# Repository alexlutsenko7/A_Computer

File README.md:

# L

Retro computers in an FPGA: an Intel/Altera Cyclone IV E (EP4CE15F23C8) on a QMTECH core board, with the RAM and
ROMs in the board's SDRAM, VGA output, a USB keyboard and an ESP32 system controller (SD card loader, on-screen
menus, Bluetooth audio). A machine menu at power-up chooses the machine:

- **LSpectrum**, a ZX Spectrum 128K with a built-in SD card tape loader that plays unmodified `.tap` / `.tzx` files,
  saves programs back to the card, and saves / loads `.z80` snapshots;
- **L64**, a Commodore 64 (PAL) with a 1541 disk drive that reads and writes `.d64` images, `.prg` / `.t64`
  loading, C64 `.tap` tapes, turbo loading and `.a64` snapshots;
- **LTari**, an Atari 800XL (**LTari 800**, 64 KB) or 130XE (**LTari 130**, 128 KB) with its own ANTIC, GTIA, POKEY
  and PIA, an SD card disk drive (`.atr`), `.xex` / `.com` programs, cartridges (`.car`) and `.a8s` snapshots.

Status (October 2026): the menu, LSpectrum, L64 and LTari work on hardware.

**Licences, what is our own work, and the complete build guide (including the C64 ROM files you have to get
yourself): [BUILDING_AND_LICENSES.md](BUILDING_AND_LICENSES.md).**

## Features

- **ZX Spectrum 128K**: T80 Z80 core at the exact 3.5469 MHz, or 28 MHz turbo; 128 KB RAM with 7FFD paging; 128K
  ROM set and DiagROM; AY-3-8912 (JT49); beeper; Kempston joystick; 50 Hz interrupt; memory contention (128K
  timing, memory and I/O cycles; not cycle-exact) and the floating bus, so most timing-critical games and border
  effects run as on the real machine.
- **Memory in SDRAM**: own 112 MHz controller for the W9825G6KH (open-row, CAS latency 2); the CPU is stepped by a
  clock enable and simply waits when the SDRAM is busy. The screen is mirrored in block RAM for the video.
- **Video**: VGA 720x576@50 (576p) or 640x480@60, 2 bits per colour, switchable at run time.
- **USB keyboard** through a CH9350-style UART module, with machine keys: DiagROM, 50/60 Hz, reset.
- **SD card tape loader** on an ESP32 system controller (firmware in C, SPI link to the FPGA):
  - on-screen browser (folders, long names, up to 320 entries), FAT16 / FAT32;
  - plays TAP and TZX (incl. turbo blocks, pure tones, pulse sequences, direct recordings, loops, jumps, calls,
    stop blocks) T-state exact, in turbo (8x) or at normal speed;
  - saves: everything the Spectrum `SAVE`s goes into a `.tap` file on the card;
  - pause, back one block, stop;
  - **snapshots**: F2 saves the whole machine as a `.z80` (version 3, 128K) at any moment; the browser loads
    `.z80` files (versions 1-3, 48K and 128K).
- **Bluetooth audio**: the same ESP32-WROOM-32 (`ESP32/v2/`, Arduino) takes the sound as I2S and sends it to Bluetooth
  speakers / headphones (A2DP), including old PIN-only devices; F3 opens the on-screen Bluetooth menu.
- **L64** (`L64/ep4_ce15/README.md`): VIC-II Kawari, T65 as 6510, the MiSTer SID 6581/8580 and CIAs, our bus, PLA
  and 1541 drive (T65, two VIAs, GCR on the fly from a track buffer the ESP32 fills from the `.d64`). The
  picture goes through a frame buffer in SDRAM: 800x600 at 60 Hz, or the C64's own 50 Hz (F8). Turbo loading (F6):
  CPU, CIAs and 1541 up to 4x while a motor runs. F2 snapshots (`.a64`). The C64 ROMs are not part of the project:
  the ESP32 installs your own ROM files from the SD card into the flash.
- **Machine menu** (`AMenu/ep4_ce15/`): the factory image at flash 0 starts a machine through the Cyclone IV remote update
  block; KEY1 in a machine returns to it.
- **Fully constrained timing**: every clock and I/O constrained, timing met at all corners.

## Hardware

| Part | Notes |
|---|---|
| QMTECH Cyclone IV core board | EP4CE15F23C8N, 50 MHz oscillator, W9825G6KH-6 SDRAM (32 MB), W25Q64 configuration flash |
| I/O board (own design, `Extra_PCB_CycloneIV/`) | 4-bit-per-colour VGA DAC, two Kempston DB9, 3.5 mm audio jack (AY + beeper, line level), USB keyboard module (UART, 3.3 V), microSD socket, sockets for the ESP32; wired to the core board's U8 |
| I/O board revision 2 (own design, `Extra_PCB_CycloneIV_R2/`, ordered 2026-11-03) | as revision 1, with everything on the board: ESP32-WROVER-E module, CP2102N USB-C console / 5 V input, CH9350L with a USB-A keyboard socket, a second USB-A (5 V for a VGA2HDMI dongle); 4 layers; same J1 to the core board's U8 |
| ESP32-WROOM-32 dev board | system controller on the I/O board: SD card, tape loader, Bluetooth audio (`ESP32/v2/README.md`) |

Pin assignments: `docs/BOARD_PINOUT.md`.

## Repository layout

AMenu, LSpectrum, L64, LTari and DDR_TEST each hold one subfolder per core board: `ep4_ce15/` (QMTECH Cyclone IV EP4CE15: all sources, simulations and tools) and `10cl025/` (QMTECH Cyclone 10 LP 10CL025YU256: the Quartus project only, generated by `tools/mk_10cl025_qsf.py`; it uses the sources of `ep4_ce15/`). The 10CL025 builds meet timing but have **not been tried on hardware** yet. An `L.jic` or `LUPDATE.BIN` is for one board only: `AMenu/<board>/output_files/`.

| Folder | Contents |
|---|---|
| `AMenu/ep4_ce15/` | machine menu shown at power-up (factory image); `L.cof` -> `output_files/L.jic`, the ready-to-program image with all machines |
| `LSpectrum/ep4_ce15/` | **The Spectrum**: Quartus project, `rtl/` (Verilog), `sim/` (Questa testbenches) |
| `ESP32/` | **the ESP32 firmware**, the same for all machines and both FPGA boards (loader + Bluetooth): `v1/` for I/O board revision 1 (in use), `v2/` for revision 2; each an Arduino sketch (`v1.ino` / `v2.ino`) with its sources in `src/` |
| `ESP32_test/` | tests of the firmware: `v1/`, `v2/` with the PC tests (`test/`) and their tools (`tools/`); `v1/` also holds the hardware test sketches `ESPLinkTest/` (SPI link) and `Test_wires/` (ESP32 <-> FPGA wiring) |
| `L64/ep4_ce15/` | **The Commodore 64**: Quartus project, `rtl/` (our bus, 1541, video; Kawari VIC-II, SID, CIA, VIA), `sim/`, `tools/` (ROM image, test disk) |
| `T65/` | 6502 core (VHDL), from the MiSTer C64 core, unchanged (`T65/SOURCE.md`) |
| `tests/` | FPGA test projects: `Test_wires/fpga/` (ESP32 <-> FPGA wiring, FPGA side; the sketch is `ESP32_test/v1/Test_wires/`), `t80_fmax/`, `jtag_rig/` (testing a core board without its I/O board: keys, status and the video picture over JTAG) |
| `T80/` | Z80 core (VHDL), from the MiSTer ZX Spectrum core, unchanged (`T80/SOURCE.md`) |
| `DDR_TEST/` | stand-alone SDRAM controller + memory test (the controller used by LSpectrum): `ep4_ce15/` for the Cyclone IV EP4CE15 core board, `10cl025/` the same test for the QMTECH Cyclone 10 LP 10CL025 core board |
| `VGA_TEST/` | stand-alone VGA test (colour bars, both video modes) |
| `Extra_PCB_CycloneIV/` | **the I/O board, revision 1**: KiCad 10 project (schematic + PDF, routed 2-layer layout, project symbols / footprints), JLCPCB order files (`jlcpcb/`: Gerbers, drill, BOM, CPL), wiring to the core board (`README.md`) |
| `Extra_PCB_CycloneIV_R2/` | **the I/O board, revision 2**: KiCad 10 project (schematic + PDF, routed 4-layer layout with GND / +3V3 planes, project footprints incl. the ESP32-WROVER-E), JLCPCB order files (`jlcpcb/`), generator / routing scripts (`tools/`), `README.md` |
| `docs/` | design notes, user documents, data sheets (see below) |

## Building

Step by step, from the tools to the SD card: [BUILDING_AND_LICENSES.md](BUILDING_AND_LICENSES.md), section 4.
Tools: Quartus Prime 25.1std Lite (Windows) for the FPGA; Arduino (core esp32 3.3.2, `arduino-cli`) for the ESP32
(libraries: `ESP32/v2/README.md`). The scripts are written for WSL on Windows and call the Windows tools;
paths are at the top of each script.

```
cd LSpectrum/ep4_ce15
quartus_sh --flow compile LSpectrum              # -> output_files/LSpectrum.sof
cd ../L64
quartus_sh --flow compile L64                # -> output_files/L64.sof
cd ../AMenu
quartus_sh --flow compile AMenu                  # machine menu
quartus_cpf -c L.cof                      # -> output_files/L.jic (menu + machines + ROMs)
cd ../..
arduino-cli compile -b esp32:esp32:esp32 -u -p COM10 ESP32/v1    # ESP32 firmware (loader + Bluetooth), I/O board revision 1
```

Flash layout (1 MB per image): menu at 0, LSpectrum at 0x100000, L64 at 0x200000, LTari 800 at 0x300000, LTari 130 at
0x400000, the Spectrum ROMs (`roms48k.hex`) at 0x500000, the Atari ROMs at 0x540000, the C64 ROMs (installed by the
ESP32) at 0x580000; ROMs are copied into SDRAM at every reset.
A change in `ESP32/v2/` needs only the ESP32 flashed again; a change in `LSpectrum/ep4_ce15/rtl/` a new compile.

## Programming

Quartus Programmer, JTAG, add `AMenu/ep4_ce15/output_files/L.jic`, tick Program/Configure, program, then
power-cycle the board. After that, `.sof` loads over JTAG are enough during development (the ROMs stay in the flash).

## Using it

The keys below are LSpectrum's; L64's (mostly the same F keys) are in `docs/L64_Keys.docx` and `L64/ep4_ce15/README.md`.

| Key | Function |
|---|---|
| F12 | tape browser (Enter plays a tape / loads a `.z80` snapshot; first line *[Save to this folder]* starts saving) |
| F2 | save a snapshot: type a name, Enter (`NAME.Z80` in the browser's current folder) |
| F12 while saving | stop saving and close the file |
| Keypad 5 / F11 | pause / continue the tape |
| Keypad - | back one block |
| F7 | stop the tape |
| F5 | memory contention and floating bus on (default) / off |
| F6 | tape speed: turbo (default) / normal |
| F8 | 60 / 50 Hz video (starts at 640x480@60; border effects line up only at 50 Hz) |
| Page Up / Page Down | browser open: page through the list; closed: move the 50 Hz frame interrupt 1/8 line to line up border effects (default 24.1, set for Aquaplane) |
| F1 held at start | the diagnostics ROM slot instead of the 128K ROM (the public image has 48K BASIC there; add DiagROM yourself with `LSpectrum/ep4_ce15/tools/mk_roms48k.py`) |
| KEY0 (board) | reset everything |
| Ctrl+Alt+Del, KEY1 (board) | back to the machine menu (Ctrl+Alt+Del when released) |

Loading: `LOAD ""` (or *Tape Loader* in the 128K menu), F12, choose the file, Enter.
Saving: F12, *[Save to this folder]*, type a name, Enter, then `SAVE` on the Spectrum as often as you like; F12 ends.
Snapshot: F2 at any moment, type a name, Enter; load it later from the F12 browser.
SD card: FAT32 or FAT16 (not exFAT).

At power-up the machine menu (`AMenu/ep4_ce15/`) appears: Up/Down + Enter, the digit, or a joystick starts a machine.

The complete key list with step-by-step usage is in `docs/LSpectrum_Keys.docx`.

## Testing

```
bash ESP32_test/v2/test/run_host_test.sh       # PC: FAT reading/writing, every TAP/TZX signal vs a Python reference, saving, .z80
bash LSpectrum/ep4_ce15/sim/run_esp_link_sim.sh           # RTL: loader hardware driven over the SPI link by an ESP32 model
bash LSpectrum/ep4_ce15/sim/run_sim.sh                    # RTL: whole machine boots the 128K ROM
bash LSpectrum/ep4_ce15/sim/run_snap_sim.sh               # RTL: snapshot freeze / restore with the real T80
bash LSpectrum/ep4_ce15/sim/run_cont_sim.sh               # RTL: memory contention (NOPs per line in contended RAM: 57 / 41)
bash LSpectrum/ep4_ce15/sim/run_float_sim.sh              # RTL: floating bus (IN A,(FF) against Fuse's 128K rule)
bash LSpectrum/ep4_ce15/sim/run_floatgame_sim.sh          # RTL: a .z80 game's floating-bus sync vs Fuse (default Sidewize)
bash AMenu/ep4_ce15/sim/run_sim.sh                        # RTL: machine menu with a model of the remote update block
bash L64/ep4_ce15/sim/run_sim.sh ROMIMAGE.mem         # RTL: whole C64 boots to READY (your own ROM image); +define+DISK: 1541 directory
bash L64/ep4_ce15/sim/run_gcr_sim.sh                  # RTL: 1541 GCR encoder / decoder
```

The PC tests need a Windows gcc (w64devkit); the simulations need Questa (Intel FPGA Starter Edition).

## Documentation

| Document | Contents |
|---|---|
| `docs/LSpectrum_Architecture.docx` | architecture of the whole machine: block diagram, clocks, memory, video, tape loader, pins, timing |
| `docs/LSpectrum_Keys.docx` | all keys and usage cases |
| `docs/LSpectrum_FKeys.docx` | short sheet of the F keys |
| `docs/L_Build_and_Install.docx` | step by step: building the three FPGA images, the one .jic, programming, the ESP32, the SD card and its ROM files, how the ROMs are used |
| `docs/L64_Keys.docx` | the machine menu and L64: all keys, the C64 keyboard layout, usage cases (ROMs, disk, tape, snapshots, 60 / 50 Hz) |
| `docs/SD_TAPE_LOADER.md` | SD tape loader: design, registers, firmware, saving, snapshots |
| `docs/SDRAM_CONTROLLER.md`, `docs/SDRAM_TUTORIAL.md` | the SDRAM controller in detail, and an SDRAM tutorial |
| `docs/T80_CEN_ANALYSIS.md` | running the T80 from a clock enable at 112 MHz |
| `docs/BOARD_PINOUT.md` | core board headers and the I/O board wiring |
| `docs/KNOWN_ISSUES.md` | open issues and limitations |
| `docs/L_Third_Party.docx` | every external core and library: origin, licence, how much of it is used |
| `docs/PLAN.md` | design decisions and development log |

## Licences

The project's own files are under the MIT licence (`LICENSE`). Third-party parts keep their own licences:

| Part | Licence |
|---|---|
| `T80/` (Z80 core, Daniel Wallner; Sorgelig) | BSD-style, see the file headers |
| `T65/` (6502 core, Daniel Wallner et al.) | BSD-style, see the file headers |
| `LSpectrum/ep4_ce15/rtl/jt49/` (AY-3-8910 core, Jose Tejada) | **GPL-3**: a bitstream that includes it is a GPL-3 work |
| `L64/ep4_ce15/rtl/vicii/` (VIC-II Kawari, Randy Rossi) | **GPL-3** |
| `L64/ep4_ce15/rtl/via/` (VIA 6522, Gideon Zweijtzer) | **GPL-3** |
| `L64/ep4_ce15/rtl/sid/`, `L64/ep4_ce15/rtl/cia/` (MiSTer C64 core) | CERN-OHL-S v2 (`sid_dac.sv`, `sid_filter.sv`) and GPL (the MiSTer C64 core) |
| `ESP32/v2/` uses ESP32-A2DP (Phil Schatzmann) | Apache-2.0 (library, not included) |
| ROM images in `LSpectrum/ep4_ce15/roms48k.hex` and `LSpectrum/ep4_ce15/sim/roms.mem` | ZX Spectrum 128 ROMs (c) Amstrad, distributed for emulator use with permission, copyright messages unchanged. Retroleum's DiagROM is not included (its licence is not known): the published image has a copy of the 48K BASIC ROM in that slot; `LSpectrum/ep4_ce15/tools/mk_roms48k.py` builds the image with your own copy |
| `LTari/ep4_ce15/roms/` (AltirraOS, Altirra BASIC, Avery Lee) | permissive notice: copying and distribution permitted, notice preserved |
| Commodore 64 / 1541 ROMs | **not included**: copyrighted; bring your own (`L64/ep4_ce15/README.md`) |
| `Extra_PCB_CycloneIV/Extra_PCB_CycloneIV.pretty/` and `Extra_PCB_CycloneIV_R2/Extra_PCB_CycloneIV_R2.pretty/`: footprints adapted from the KiCad libraries (D-Sub 15 HD, pin headers); revision 2's ESP32-WROVER-E footprint is own work from Espressif's land pattern | CC-BY-SA 4.0 with the KiCad library exception (designs made with them, the board files and Gerbers included, are not bound by it); the rest of the boards is MIT |

Because of the GPL-3 parts, the LSpectrum and L64 bitstreams (and `L.jic`) are GPL-3 works. Details, the
notices the BSD-style cores require, and what was changed in external code: [BUILDING_AND_LICENSES.md](BUILDING_AND_LICENSES.md);
how much of each part is used: `docs/L_Third_Party.docx`.

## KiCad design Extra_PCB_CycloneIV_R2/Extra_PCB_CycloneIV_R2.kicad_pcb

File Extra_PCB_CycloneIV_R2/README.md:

# Extra_PCB_CycloneIV_R2 — I/O board, revision 2

KiCad 10 project for the second revision of the L I/O board (revision 1 = `../Extra_PCB_CycloneIV/`, as built).
The board sits beside the QMTECH Cyclone IV core board and is wired to its U8 through J1, exactly as revision 1
(same J1 pinout, same pair-swapped wiring), so the FPGA images do not change. The ESP32 firmware is
`ESP32/v2` (control UART on other pins, PSRAM build).

J1 also fits the **QMTECH Cyclone 10 LP 10CL025 core board** (10CL025YU256, schematic V1 2023-11-09). The board is the
same size (84.1 x 67.1 mm), and its U8 sits at the same place and the same way round: pin 1 at the left end of the outer
row, VIN at the right end. Its U8 power pins match (1/2 GND, 3/4 3V3, 61/62 GND, 63/64 VIN), except that pins **5/6 are
GND** on the 10CL025 (clock inputs on the EP4CE15). J1 leaves 5/6 unconnected, and they must stay that way. U8 pins 7-60
are all 3.3 V I/O on both boards. The 10CL025 needs its own FPGA pin list (other ball names).

Status (2026-11-03): **schematic** generated from `tools/design.py`, drawn with wires, then edited in KiCad (the KiCad
schematic is the source of truth; `tools/check_net.py` checks it against `design.py`). **PCB: 4 layers, placed and fully
routed**: DRC 0 unconnected, 0 clearance errors, 0 schematic parity issues; only silkscreen text warnings left (reference
texts not tidied yet). The KiCad board is the source of truth (mounting holes moved by the user). Placement backup
(before routing): `archive/2026-11-03_before_routing/`.

## Board rules and checks

- Copper to board edge 0.3 mm (JLCPCB); the microSD socket J7 sits 0.25 mm inside the left edge for this.
- No vias inside small SMD pads; vias only in the large GND pads of U2 (pad 39) and U3 and in U1's tab.
- Silkscreen references 0.8 mm / 0.13 mm, each beside its part (`tools/silk.py`), connector outlines clipped at the
  board edge (DRC therefore notes "footprint differs from library" for J2-J6).
- The ESP32-WROVER-E footprint matches the datasheet land pattern (Fig. 15): pad size, pitch, pin 1 / pin 19 and
  GND pad position.
- Checks: ERC 0 / 0, `tools/check_net.py` PASS, DRC 0 errors, 0 unconnected, 0 schematic parity issues.

## Parts choice

Most resistors and small capacitors are JLCPCB **Basic** parts (no per-line fee). Extended parts: the VGA DAC, 523 / 1.05k / 2.1k /
4.22k per colour (full scale 0.70 V into 75 Ohm, steps even within about 0.02 LSB), 6p8 on the VGA lines, 68 Ohm in the AY low-pass
(23 kHz with 0.1 uF), 47.5k in the CP2102N VBUS divider, ESP32-WROVER-E, CP2102N, CH9350L, LDL1117S33R (kept over the Basic
AMS1117 for its lower dropout and better PSRR), USBLC6-2SC6, PTS810 buttons, and the connectors. USB-A J8 / J9:
CONNFLY DS1095-WNR0 (C19944603). Older states of the board and its order files are in `archive/` (the ordered set: `archive/2026-11-03_as_ordered/`).

## JLCPCB order files (`jlcpcb/`, made by `python3 tools/jlc_export.py` in WSL)

Gerbers for 4 layers (F.Cu, In1.Cu GND, In2.Cu +3V3, B.Cu) + drill, BOM and CPL with LCSC numbers checked 2026-11-03
(identity checked on lcsc.com / jlcpcb.com; stock shows in JLCPCB's BOM check). Order: 4 layers, 1.6 mm, default
stack-up; option "via in pad, epoxy filled + capped" for the vias in the ESP32 / CP2102N centre pads. Check part
rotations in JLCPCB's placement preview (custom footprints U2, J2; U3 is rotated 180 deg). J1 and the holes are not
in the BOM / CPL.

## PCB layers and routing

| Layer | Use |
|---|---|
| F.Cu | signals + fan-out of the plane nets (no copper under the ESP32 body except its pads, see rule areas) |
| In1.Cu | **GND plane** (power layer) |
| In2.Cu | **+3V3 plane** (power layer) |
| B.Cu | signals |

- Net classes (`.kicad_pro`): signals 0.2 mm / 0.15 mm clearance, +3V3 0.3 mm, +5V and VBUS_C 0.4 mm, vias 0.6 / 0.3 mm;
  board minimum track 0.1 mm (short neck-downs at the 0.5 mm pitch CP2102N / CH9350L pins; JLCPCB minimum 0.09 mm).
- Every SMD pad on GND / +3V3 has its own via to its plane (`tools/route.py fan`); the ESP32's pad 39 has 4 GND vias
  (in the hole of the top-layer rule area); U3's centre pad connects to GND through pin 2's track and its own vias.
- USB-C corner (`tools/usbc.py`, by hand): D+ pads joined left of the pads, D- pads joined right of them under the
  connector (track only), VBUS pad pairs through vias to a B.Cu joiner and a via under U5 to its pin 5, CC1 through a
  tented via under the connector, J5's GND pins straight to the shield pads.
- CP2102N (U3) rotated 180 deg (user) so D+ / D- face the ESD part; D- crosses D+ through a B.Cu hop (`tools/dmfix.py`).
- The rest: FreeRouting 2.5.0 (plane nets ignored), driven by `tools/route.py` (prep / fan / free / import / unlock).

## PCB placement

Revision 1's outline (84.1 x 83.4 mm) and J1 position. Connectors on the edges:

| Edge | Top to bottom / left to right |
|---|---|
| Top | DB9 joystick 1 (J4), DB9 joystick 2 (J6), audio jack J3 (opening up); the corner beyond it is antenna clearance |
| Left | USB 2 J9 (5 V for a VGA2HDMI dongle) beside VGA J2, then VGA J2, microSD J7 |
| Right | ESP32-WROVER-E U2 with the antenna end 1 mm inside the edge (nothing sticks out; keep-out in the footprint), USB-C J5, USB 1 J8 (keyboard) |
| Bottom | J1 host connector (as revision 1) |

Groups: joystick pull-ups under their DB9s; VGA DAC resistors and 6p8 caps beside J2; microSD pull-ups beside J7;
audio filter left of the ESP32; ESP32 decoupling and EN RC above its pins 2 / 3, left of the antenna; CP2102N, ESD, CC resistors and
the auto-reset transistors between the ESP32 and USB-C; EN / BOOT buttons left of them; LDO in the middle; CH9350L
with the ESD part and bulk caps beside J8. Mounting holes H1-H4 inside the board (the corners hold connectors or the antenna clearance).
Rule area "ESP32 antenna clearance" (all 4 copper layers: no tracks, vias, pads, pour or parts): x 127.2 to the right edge, y 76.0-119.0 = the antenna, 15 mm of edge beside it on the side away from the feed point (Espressif "Keepout Zone for ESP32 Module's Antenna (Antenna feed point on the right)"; the feed side faces USB-C) and the strip down to USB-C.
Rule area "ESP32 body: top layer clear" (F.Cu only: no tracks, vias or pour; pads allowed) between the module's pad rows up to the antenna, with a hole around pad 39 (GND) for its vias: nothing but the module's own pads touches its underside; B.Cu under the module is for the GND fill (user's choice after a XIAO board failed on a GND fill).
The ESP32 footprint has no via pads: GND vias under its centre pad are added when routing.

Built by `tools/mk_pcb.py build` (KiCad python) from the netlist (`kicad-cli sch export netlist --format kicadxml -o
netlist.xml`) and `tools/placement.py`. Once the board is edited in KiCad, the KiCad file is the source of truth: do
not rebuild over it.

## What changes against revision 1

| Revision 1 | Revision 2 |
|---|---|
| ESP32 DevKit on two 1x15 sockets | **ESP32-WROVER-E-N16R8** module (U2, JLCPCB C529589: 16 MB flash, 8 MB PSRAM for large folder lists); the DevKit's GPIOs except the control UART (IO16 / IO17 drive the PSRAM): RX2 on IO27, TX2 on IO21; antenna at a board edge |
| (console = the DevKit's USB) | **CP2102N** (U3) on **USB-C** (J5), DTR/RTS auto-reset (Q1, Q2), EN / BOOT buttons |
| keyboard module on J5 (4-pin header) | **CH9350L** (U4) + right-angle **USB-A** J8 for the keyboard at the board edge near the CH9350L; a second right-angle USB-A J9 beside the VGA socket carries **5 V only** (power for a VGA2HDMI dongle) |
| 5 V from the core board (J1 63/64) | **5 V from USB-C** on this board, straight to +5V (no diode), which also feeds the core board via J1 63/64. Power the system from USB-C **or** the core board's DC jack, never both (no back-feed protection) |
| K7803 switching module | **LDL1117S33R** LDO (U1, 1.2 A, SOT-223) |
| THT audio capacitors | SMD (same circuit) |

Unchanged: VGA (4-bit DAC per colour, J2 CONNFLY DS1038), two DB9 joysticks (J4, J6, 3k3 pull-ups), microSD (J7, on the
ESP32), audio line-out jack (J3), four M3 holes.

## Circuit notes

- **USB-C (J5)**: 5.1k on CC1 / CC2 (a USB-C source gives 5 V), USBLC6-2SC6 (U5) on D+/D-. VBUS is +5V directly (no
  diode): supply the system from USB-C (a self-powered hub or charger, >= 1.5 A) or from the core board's input, not both.
- **CP2102N (U3)**: self-powered from +3V3 (VREGIN = VDD = VIO), VBUS sensed through 22k / 47.5k (3.4 V at 5 V), RST pulled up (1k).
  TXD -> ESP32 RXD0, RXD <- TXD0. Auto-reset as on the DevKit: Q1 (base from DTR, emitter RTS) pulls EN,
  Q2 (base from RTS, emitter DTR) pulls IO0.
- **ESP32 (U2)**: EN 10k + 1 uF, IO0 10k pull-up, 22 uF + 0.1 uF. GPIOs: link SCK 14, MOSI 13, CS 33, MISO 35, IRQ 34;
  I2S BCLK 26, LRCK 25, DATA 22; control UART RX2 27 <- BT_TX, TX2 21 -> BT_RX (the DevKit of revision 1: 16 / 17);
  SD SCK 18, MISO 19, MOSI 23, CS 5. Footprint `ESP32-WROVER-E` (tools/fp_wrover.py) from the datasheet v2.4
  land pattern: 19 pads per side, pitch 1.27, pads 1.5 x 0.9 at x +-8.75, pin 1 7.44 mm below the antenna end,
  3.7 mm GND pad; antenna keep-out zone (7.44 mm, no copper on either layer) in the footprint. Firmware: `ESP32/v2`
  (UART2 on 27 / 21), built with PSRAM enabled; the revision 1 DevKit takes `ESP32/v1` (16 / 17).
- **CH9350L (U4)**, WCH datasheet V2.6: VIN5 from +5V (0.1 uF), VDD33 4.7 uF (internal regulator), RST to GND, SEL / S0 /
  S1 / BAUD0 / BAUD1 / xOSC open (internal pull-ups: keyboard / mouse side, state 0, 115200 baud) = the frames
  `zx_keyboard.v` already decodes. TXD -> KB_IN, RXD <- KB_OUT (the FPGA reads KB_OUT AND KB_IN). Port 2 (HP/HM) is
  not used (a keyboard and a mouse together need a USB hub on J8). J8: 5 V straight from +5V (no fuse: a short on J8 / J9 trips the upstream USB port's current limit and resets the board), 100 uF + 0.1 uF, USBLC6-2SC6.
  J9 (5 V only): 5 V from +5V, 100 uF + 0.1 uF, data pins open.
- **3.3 V**: LDL1117S33R (600 mV max dropout at 1.2 A), from +5V.

## Files

| Path | Role |
|---|---|
| `Extra_PCB_CycloneIV_R2.kicad_sch` / `.pdf` | Schematic, ANSI B (11 x 17 in) |
| `Extra_PCB_CycloneIV_R2.kicad_sym` | Project symbols: DB15_Female_HighDensity (from revision 1), CH9350L (new, LQFP-48), ESP32-WROVER-E (KiCad's WROOM-32E symbol, pins 27 / 28 NC) |
| `Extra_PCB_CycloneIV_R2.pretty/` | Project footprints: CONNFLY DS1038 VGA, 2x32 J1 (rows swapped) from revision 1; ESP32-WROVER-E (new) |
| `tools/fp_wrover.py` | Writes the ESP32-WROVER-E footprint from the datasheet land pattern |
| `tools/design.py` | Component list and nets (single source) |
| `tools/gen_sch.py` | Generates the schematic + symbol library from design.py: parts of one circuit joined by wires (`w()` calls), labels for the nets between blocks; checks that no pin, stub or wire touches another net |
| `tools/check_net.py [file]` | Netlist of the schematic (kicad-cli) against design.py |
| `tools/mk_pcb.py`, `tools/placement.py` | KiCad python: `info` (footprint sizes), `build` (board from the netlist + placement, no tracks), `pads <pcb> refs...` |
| `tools/route.py`, `tools/usbc.py`, `tools/u3fix.py`, `tools/dmfix.py` | KiCad python: the routing steps above (history of how the board was routed; the board itself is the source of truth now) |

The generator is for the first version only: once the schematic is edited in KiCad, the KiCad files are the source.

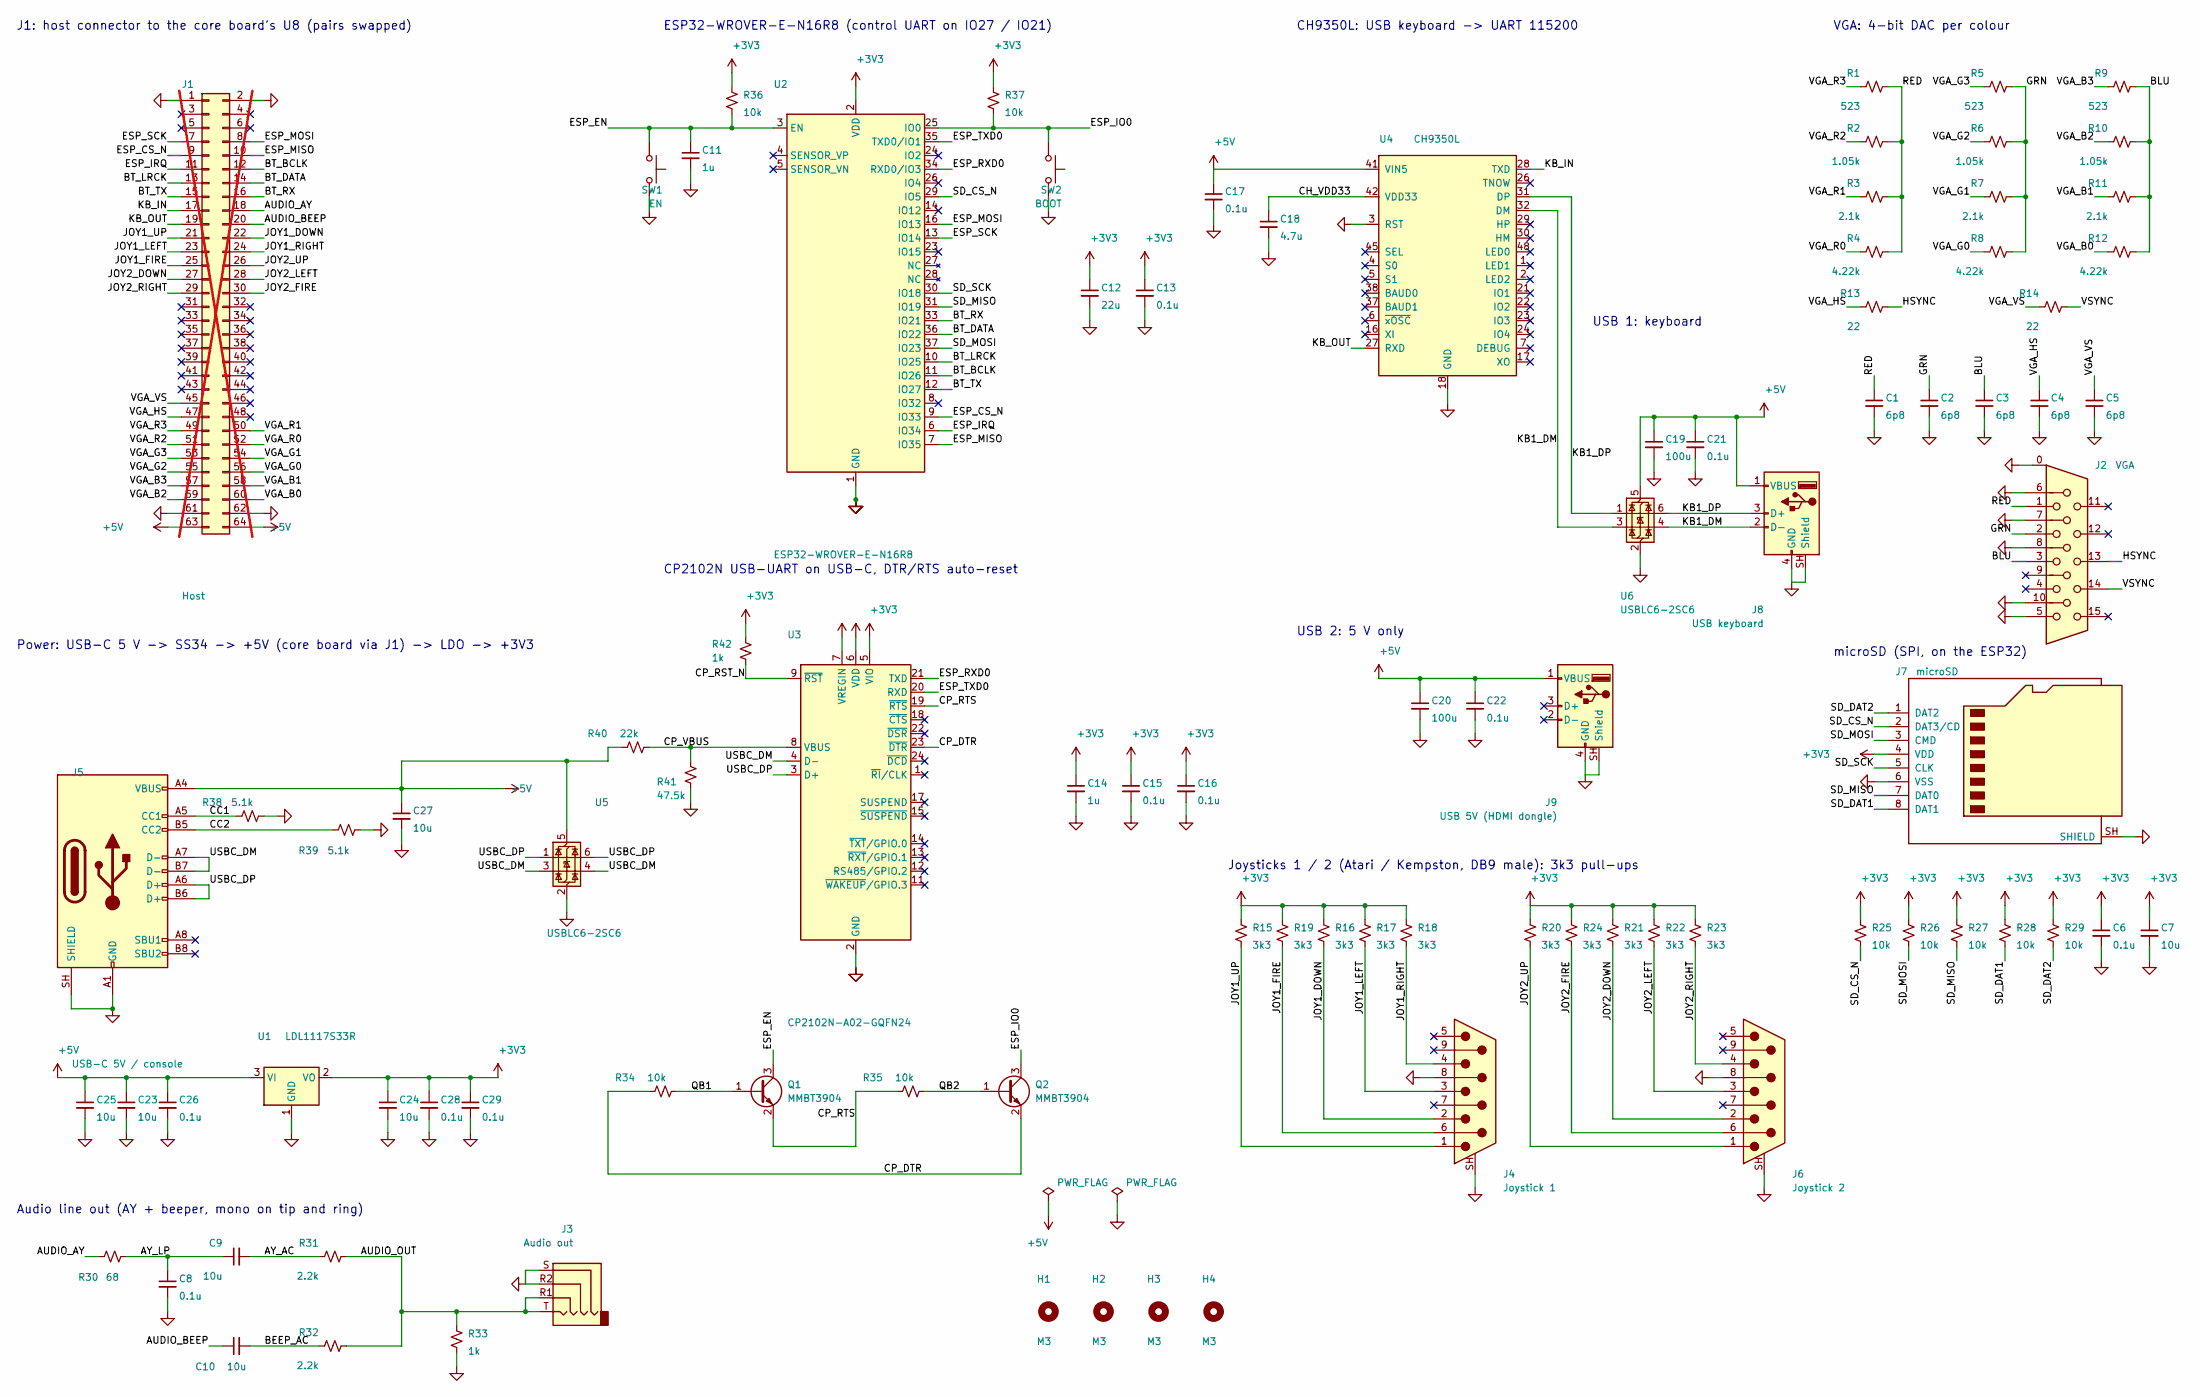
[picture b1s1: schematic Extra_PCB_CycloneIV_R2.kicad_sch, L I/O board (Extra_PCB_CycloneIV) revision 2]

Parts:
C1, C2, C3, C4, C5: 6p8; C_0603_1608Metric
C6, C8, C13, C15, C16, C17, C21, C22, C26, C28, C29: 0.1u; C_0603_1608Metric
C7, C9, C10, C23, C24, C25, C27: 10u; C_0805_2012Metric
C11, C14: 1u; C_0603_1608Metric
C12: 22u; C_0805_2012Metric
C18: 4.7u; C_0603_1608Metric
C19, C20: 100u; C_1206_3216Metric
H1, H2, H3, H4: M3; MountingHole_3.2mm_M3
J1: Host; PinHeader_2x32_P2.54mm_Vertical_RowsSwapped; not fitted
J2: VGA; DSUB-15-HD_Socket_Horizontal_P2.29x2.54mm_CONNFLY_DS1038; MPN DS1038-15FBNSiA74-0CC
J3: Audio out; Jack_3.5mm_KoreanHropartsElec_PJ-320D-4A_Horizontal; MPN PJ-320D-4A
J4: Joystick 1; DSUB-9_Pins_Horizontal_P2.77x2.84mm_EdgePinOffset7.70mm_Hou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; MPN DS1037-09MNAKT74-0CC
J5: USB-C 5V / console; USB_C_Receptacle_HRO_TYPE-C-31-M-12; MPN TYPE-C-31-M-12
J6: Joystick 2; DSUB-9_Pins_Horizontal_P2.77x2.84mm_EdgePinOffset7.70mm_Hou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; MPN DS1037-09MNAKT74-0CC
J7: microSD; microSD_HC_Molex_104031-0811; MPN 104031-0811
J8: USB keyboard; USB_A_Connfly_DS1095; MPN DS1095-WNR0
J9: USB 5V (HDMI dongle); USB_A_Connfly_DS1095; MPN DS1095-WNR0
Q1, Q2: MMBT3904; SOT-23; MPN MMBT3904
R1, R5, R9: 523; R_0603_1608Metric
R2, R6, R10: 1.05k; R_0603_1608Metric
R3, R7, R11: 2.1k; R_0603_1608Metric
R4, R8, R12: 4.22k; R_0603_1608Metric
R13, R14: 22; R_0603_1608Metric
R15, R16, R17, R18, R19, R20, R21, R22, R23, R24: 3k3; R_0603_1608Metric
R25, R26, R27, R28, R29, R34, R35, R36, R37: 10k; R_0603_1608Metric
R30: 68; R_0603_1608Metric
R31, R32: 2.2k; R_0603_1608Metric
R33, R42: 1k; R_0603_1608Metric
R38, R39: 5.1k; R_0603_1608Metric
R40: 22k; R_0603_1608Metric
R41: 47.5k; R_0603_1608Metric
SW1: EN; SW_SPST_PTS810; MPN PTS810SJM250SMTRLFS
SW2: BOOT; SW_SPST_PTS810; MPN PTS810SJM250SMTRLFS
U1: LDL1117S33R; SOT-223-3_TabPin2; MPN LDL1117S33R
U2: ESP32-WROVER-E-N16R8; ESP32-WROVER-E; MPN ESP32-WROVER-E-N16R8
U3: CP2102N-A02-GQFN24; QFN-24-1EP_4x4mm_P0.5mm_EP2.6x2.6mm; MPN CP2102N-A02-GQFN24R
U4: CH9350L; LQFP-48_7x7mm_P0.5mm; MPN CH9350L
U5, U6: USBLC6-2SC6; SOT-23-6; MPN USBLC6-2SC6

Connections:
+3V3: C6.1, C7.1, C12.1, C13.1, C14.1, C15.1, C16.1, C24.1, C28.1, C29.1, J7.4 (VDD), R15.1, R16.1, R17.1, R18.1, R19.1, R20.1, R21.1, R22.1, R23.1, R24.1, R25.1, R26.1, R27.1, R28.1, R29.1, R36.1, R37.1, R42.1, U1.2 (VO), U2.2 (VDD), U3.5 (VIO), U3.6 (VDD), U3.7 (VREGIN)
+5V: C17.1, C19.1, C20.1, C21.1, C22.1, C23.1, C25.1, C26.1, C27.1, J1.63, J1.64, J5.A4 (VBUS), J5.A9 (VBUS), J5.B4 (VBUS), J5.B9 (VBUS), J8.1 (VBUS), J9.1 (VBUS), R40.1, U1.3 (VI), U4.41 (VIN5), U5.5 (VBUS), U6.5 (VBUS)
/AUDIO_AY: J1.18, R30.1
/AUDIO_BEEP: C10.1, J1.20
/AUDIO_OUT: J3.R1, J3.T, R31.2, R32.2, R33.1
/AY_AC: C9.2, R31.1
/AY_LP: C8.1, C9.1, R30.2
/BEEP_AC: C10.2, R32.1
/BLU: C3.1, J2.3, R9.2, R10.2, R11.2, R12.2
/BT_BCLK: J1.12, U2.11 (IO26)
/BT_DATA: J1.14, U2.36 (IO22)
/BT_LRCK: J1.13, U2.10 (IO25)
/BT_RX: J1.16, U2.33 (IO21)
/BT_TX: J1.15, U2.12 (IO27)
/CC1: J5.A5 (CC1), R38.1
/CC2: J5.B5 (CC2), R39.1
/CH_VDD33: C18.1, U4.42 (VDD33)
/CP_DTR: Q2.2 (E), R34.1, U3.23 (~DTR)
/CP_RST_N: R42.2, U3.9 (~RST)
/CP_RTS: Q1.2 (E), R35.1, U3.19 (~RTS)
/CP_VBUS: R40.2, R41.1, U3.8 (VBUS)
/ESP_CS_N: J1.9, U2.9 (IO33)
/ESP_EN: C11.1, Q1.3 (C), R36.2, SW1.1, U2.3 (EN)
/ESP_IO0: Q2.3 (C), R37.2, SW2.1, U2.25 (IO0)
/ESP_IRQ: J1.11, U2.6 (IO34)
/ESP_MISO: J1.10, U2.7 (IO35)
/ESP_MOSI: J1.8, U2.16 (IO13)
/ESP_RXD0: U2.34 (RXD0/IO3), U3.21 (TXD)
/ESP_SCK: J1.7, U2.13 (IO14)
/ESP_TXD0: U2.35 (TXD0/IO1), U3.20 (RXD)
/GRN: C2.1, J2.2, R5.2, R6.2, R7.2, R8.2
/HSYNC: J2.13, R13.2
/JOY1_DOWN: J1.22, J4.2, R16.2
/JOY1_FIRE: J1.25, J4.6, R19.2
/JOY1_LEFT: J1.23, J4.3, R17.2
/JOY1_RIGHT: J1.24, J4.4, R18.2
/JOY1_UP: J1.21, J4.1, R15.2
/JOY2_DOWN: J1.27, J6.2, R21.2
/JOY2_FIRE: J1.30, J6.6, R24.2
/JOY2_LEFT: J1.28, J6.3, R22.2
/JOY2_RIGHT: J1.29, J6.4, R23.2
/JOY2_UP: J1.26, J6.1, R20.2
/KB1_DM: J8.2 (D-), U4.32 (DM), U6.3 (I/O2), U6.4 (I/O2)
/KB1_DP: J8.3 (D+), U4.31 (DP), U6.1 (I/O1), U6.6 (I/O1)
/KB_IN: J1.17, U4.28 (TXD)
/KB_OUT: J1.19, U4.27 (RXD)
/QB1: Q1.1 (B), R34.2
/QB2: Q2.1 (B), R35.2
/RED: C1.1, J2.1, R1.2, R2.2, R3.2, R4.2
/SD_CS_N: J7.2 (DAT3/CD), R25.2, U2.29 (IO5)
/SD_DAT1: J7.8 (DAT1), R28.2
/SD_DAT2: J7.1 (DAT2), R29.2
/SD_MISO: J7.7 (DAT0), R27.2, U2.31 (IO19)
/SD_MOSI: J7.3 (CMD), R26.2, U2.37 (IO23)
/SD_SCK: J7.5 (CLK), U2.30 (IO18)
/USBC_DM: J5.A7 (D-), J5.B7 (D-), U3.4 (D-), U5.3 (I/O2), U5.4 (I/O2)
/USBC_DP: J5.A6 (D+), J5.B6 (D+), U3.3 (D+), U5.1 (I/O1), U5.6 (I/O1)
/VGA_B0: J1.60, R12.1
/VGA_B1: J1.58, R11.1
/VGA_B2: J1.59, R10.1
/VGA_B3: J1.57, R9.1
/VGA_G0: J1.56, R8.1
/VGA_G1: J1.54, R7.1
/VGA_G2: J1.55, R6.1
/VGA_G3: J1.53, R5.1
/VGA_HS: C4.1, J1.47, R13.1
/VGA_R0: J1.52, R4.1
/VGA_R1: J1.50, R3.1
/VGA_R2: J1.51, R2.1
/VGA_R3: J1.49, R1.1
/VGA_VS: C5.1, J1.45, R14.1
/VSYNC: J2.14, R14.2
GND: C1.2, C2.2, C3.2, C4.2, C5.2, C6.2, C7.2, C8.2, C11.2, C12.2, C13.2, C14.2, C15.2, C16.2, C17.2, C18.2, C19.2, C20.2, C21.2, C22.2, C23.2, C24.2, C25.2, C26.2, C27.2, C28.2, C29.2, J1.1, J1.2, J1.61, J1.62, J2.0 (GND), J2.5, J2.6, J2.7, J2.8, J2.10, J3.R2, J3.S, J4.8, J4.SH (PAD), J5.A1 (GND), J5.A12 (GND), J5.B1 (GND), J5.B12 (GND), J5.SH (SHIELD), J6.8, J6.SH (PAD), J7.6 (VSS), J7.SH (SHIELD), J8.4 (GND), J8.SH (Shield), J9.4 (GND), J9.SH (Shield), R33.2, R38.2, R39.2, R41.2, SW1.2, SW2.2, U1.1 (GND), U2.1 (GND), U2.15 (GND), U2.38 (GND), U2.39 (GND), U3.2 (GND), U3.25 (GND), U4.3 (RST), U4.18 (GND), U5.2 (GND), U6.2 (GND)

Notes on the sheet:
Audio line out (AY + beeper, mono on tip and ring)
Joysticks 1 / 2 (Atari / Kempston, DB9 male): 3k3 pull-ups
microSD (SPI, on the ESP32)
VGA: 4-bit DAC per colour
Power: USB-C 5 V -> SS34 -> +5V (core board via J1) -> LDO -> +3V3
USB 2: 5 V only
ESP32-WROVER-E-N16R8 (control UART on IO27 / IO21)
J1: host connector to the core board's U8 (pairs swapped)
CP2102N USB-UART on USB-C, DTR/RTS auto-reset
CH9350L: USB keyboard -> UART 115200
USB 1: keyboard

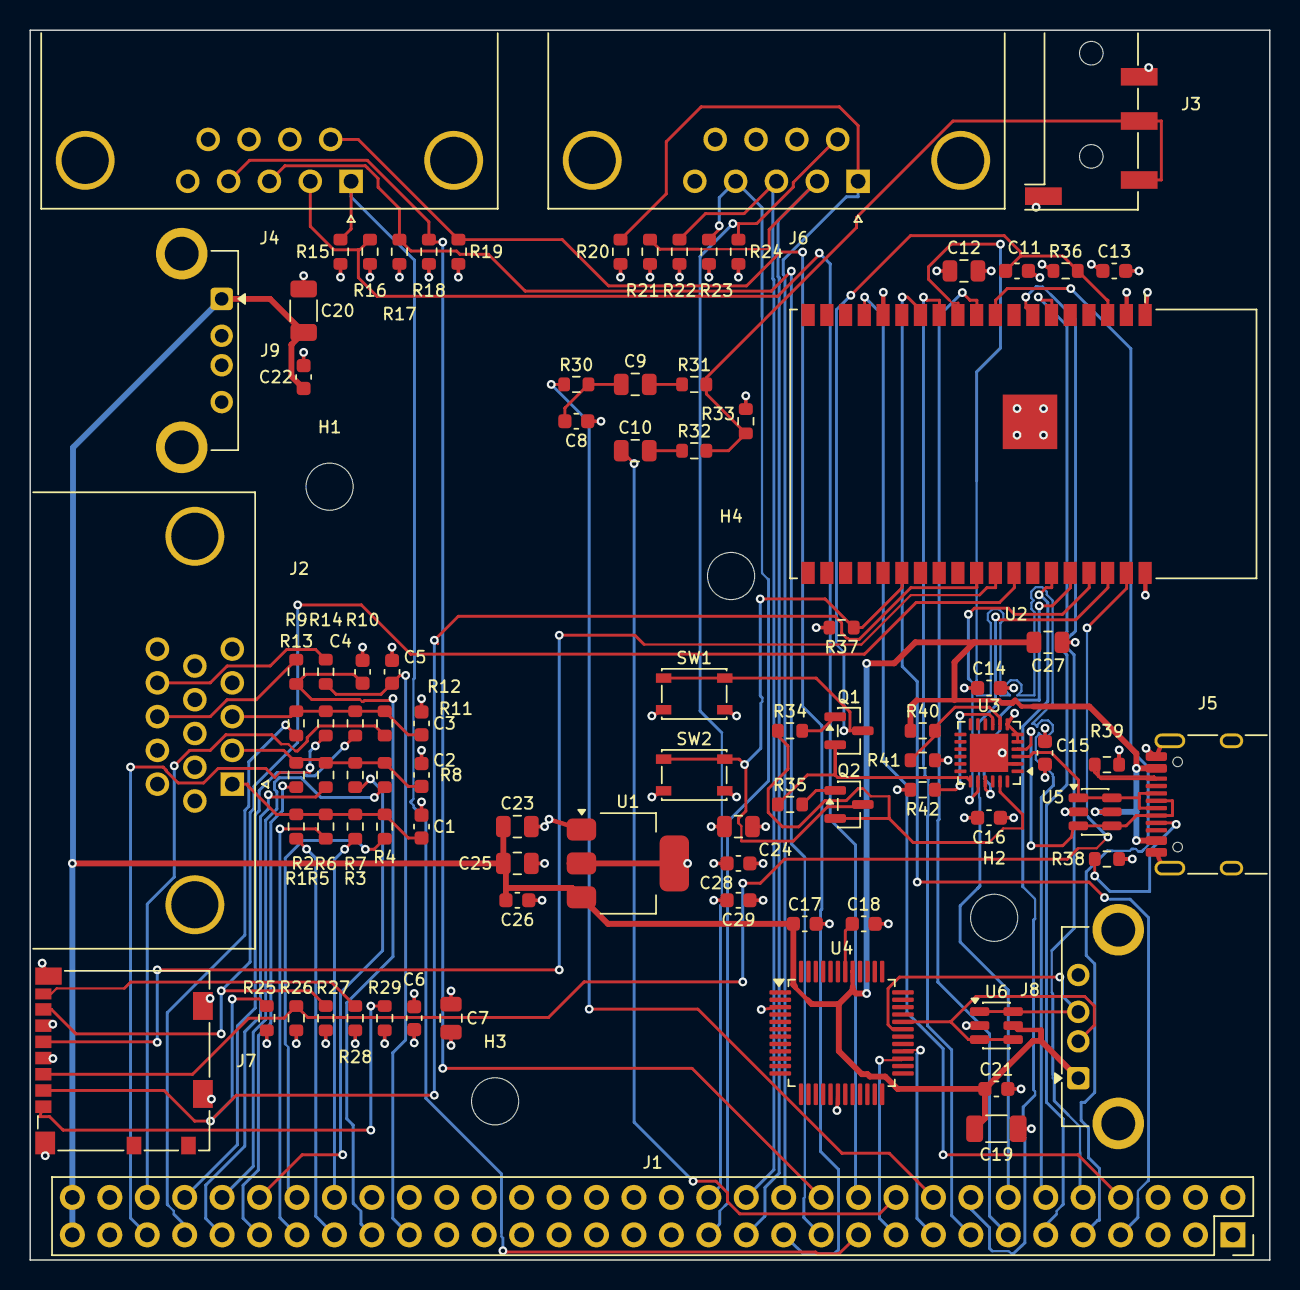
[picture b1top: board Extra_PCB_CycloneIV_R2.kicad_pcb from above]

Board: 4 copper layers, 84.1 x 83.4 mm, 94 parts (0 on the bottom side), 73 nets.

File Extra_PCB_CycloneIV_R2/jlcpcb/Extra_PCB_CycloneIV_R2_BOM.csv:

Comment,Designator,Footprint,LCSC Part #
6p8,"C1,C2,C3,C4,C5",C_0603_1608Metric,C318672
0.1u,"C6,C8,C13,C15,C16,C17,C21,C22,C26,C28,C29",C_0603_1608Metric,C14663
10u,"C7,C9,C10,C23,C24,C25,C27",C_0805_2012Metric,C15850
1u,"C11,C14",C_0603_1608Metric,C15849
22u,C12,C_0805_2012Metric,C45783
4.7u,C18,C_0603_1608Metric,C19666
100u,"C19,C20",C_1206_3216Metric,C15008
VGA,J2,DSUB-15-HD_Socket_Horizontal_P2.29x2.54mm_CONNFLY_DS1038,C75754
Audio out,J3,Jack_3.5mm_KoreanHropartsElec_PJ-320D-4A_Horizontal,C95562
Joystick 2 / Joystick 1,"J4,J6",DSUB-9_Pins_Horizontal_P2.77x2.84mm_EdgePinOffset7.70mm_Housed_MountingHolesOffset9.12mm,C75750
USB-C 5V / console,J5,USB_C_Receptacle_HRO_TYPE-C-31-M-12,C165948
microSD,J7,microSD_HC_Molex_104031-0811,C585350
USB 5V (HDMI dongle) / USB keyboard,"J8,J9",USB_A_Connfly_DS1095,C19944603
MMBT3904,"Q1,Q2",SOT-23,C20526
523,"R1,R5,R9",R_0603_1608Metric,C23199
1.05k,"R2,R6,R10",R_0603_1608Metric,C22832
2.1k,"R3,R7,R11",R_0603_1608Metric,C22902
4.22k,"R4,R8,R12",R_0603_1608Metric,C23042
22,"R13,R14",R_0603_1608Metric,C23345
3k3,"R15,R16,R17,R18,R19,R20,R21,R22,R23,R24",R_0603_1608Metric,C22978
10k,"R25,R26,R27,R28,R29,R34,R35,R36,R37",R_0603_1608Metric,C25804
68,R30,R_0603_1608Metric,C27592
2.2k,"R31,R32",R_0603_1608Metric,C4190
1k,"R33,R42",R_0603_1608Metric,C21190
5.1k,"R38,R39",R_0603_1608Metric,C23186
22k,R40,R_0603_1608Metric,C31850
47.5k,R41,R_0603_1608Metric,C23061
BOOT / EN,"SW1,SW2",SW_SPST_PTS810,C116501
LDL1117S33R,U1,SOT-223-3_TabPin2,C435835
ESP32-WROVER-E-N16R8,U2,ESP32-WROVER-E,C529589
CP2102N-A02-GQFN24,U3,QFN-24-1EP_4x4mm_P0.5mm_EP2.6x2.6mm,C969151
CH9350L,U4,LQFP-48_7x7mm_P0.5mm,C109472
USBLC6-2SC6,"U5,U6",SOT-23-6,C7519

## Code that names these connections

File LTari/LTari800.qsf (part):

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
# Extra_PCB_CycloneIV I/O board: its J1 is wired to U8 with each pin pair swapped
# (J1 pin 2k-1 -> U8 pin 2k, J1 pin 2k -> U8 pin 2k-1). Comment: I/O board J1 pin / U8 pin.
set_location_assignment PIN_AB13 -to ESP_SCK        # J1.7 / U8.8
set_location_assignment PIN_AA13 -to ESP_MOSI       # J1.8 / U8.7
set_location_assignment PIN_AB14 -to ESP_CS_N       # J1.9 / U8.10
set_location_assignment PIN_AA14 -to ESP_MISO       # J1.10 / U8.9
set_location_assignment PIN_AB15 -to ESP_IRQ        # J1.11 / U8.12
set_location_assignment PIN_AA15 -to BT_BCLK        # J1.12 / U8.11
set_location_assignment PIN_AB16 -to BT_LRCK        # J1.13 / U8.14
set_location_assignment PIN_AA16 -to BT_DATA        # J1.14 / U8.13
set_location_assignment PIN_AB17 -to BT_TX          # J1.15 / U8.16
set_location_assignment PIN_AA17 -to BT_RX          # J1.16 / U8.15
set_location_assignment PIN_AB18 -to KB_IN          # J1.17 / U8.18
set_location_assignment PIN_AA18 -to AUDIO_AY       # J1.18 / U8.17
set_location_assignment PIN_AB19 -to KB_OUT         # J1.19 / U8.20
set_location_assignment PIN_AA19 -to AUDIO_BEEP     # J1.20 / U8.19
set_location_assignment PIN_AB20 -to JOY1_UP_N      # J1.21 / U8.22
set_location_assignment PIN_AA20 -to JOY1_DOWN_N    # J1.22 / U8.21
set_location_assignment PIN_Y21 -to JOY1_LEFT_N    # J1.23 / U8.24
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set_location_assignment PIN_V22 -to JOY2_LEFT_N    # J1.28 / U8.27
set_location_assignment PIN_U21 -to JOY2_RIGHT_N   # J1.29 / U8.30
set_location_assignment PIN_U22 -to JOY2_FIRE_N    # J1.30 / U8.29
set_location_assignment PIN_H21 -to VGA_VS         # J1.45 / U8.46
set_location_assignment PIN_F21 -to VGA_HS         # J1.47 / U8.48
# sync pins at the weakest drive (3.3-V LVCMOS, 2 mA: slower edges): the HSYNC edge coupled onto the colour lines (~30 mV spike 40 pixels after the
# active area), and monitors auto-adjusted to it as the picture edge (a line at the right)
set_instance_assignment -name CURRENT_STRENGTH_NEW 2MA -to VGA_HS
set_instance_assignment -name CURRENT_STRENGTH_NEW 2MA -to VGA_VS
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
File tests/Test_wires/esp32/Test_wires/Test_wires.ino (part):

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
// FPGA -> ESP32; the FPGA marks frames on these with id C1..C4 (in this order)
static const Wire RET[4] = {
    {35, "GPIO35 (D35)", "R1", "U7.7",  "ESP_MISO"},
    {34, "GPIO34 (D34)", "R2", "U7.8",  "ESP_IRQ"},
    {22, "GPIO22 (D22)", "F1", "U7.19", "BT_DATA"},
    {16, "GPIO16 (RX2)", "F2", "U7.20", "BT_TX"},
};
// ESP32 -> FPGA; bit n of the FPGA's level byte / counter n
static const Wire FWD[6] = {
    {14, "GPIO14 (D14)", "P1", "U7.9",  "ESP_SCK"},
    {13, "GPIO13 (D13)", "P2", "U7.10", "ESP_MOSI"},
    {33, "GPIO33 (D33)", "N1", "U7.11", "ESP_CS_N"},
    {26, "GPIO26 (D26)", "H1", "U7.17", "BT_BCLK"},
    {25, "GPIO25 (D25)", "H2", "U7.18", "BT_LRCK"},
    {17, "GPIO17 (TX2)", "E1", "U7.21", "BT_RX"},
};
static const int SD_SCK = 18, SD_MISO = 19, SD_MOSI = 23, SD_CS = 5;

SPIClass sdspi(VSPI);
SPIClass fastspi(HSPI);
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    for (uint32_t f : hz) {
        sdspi.end();
        sdspi.begin(SD_SCK, SD_MISO, SD_MOSI, SD_CS);
        gpio_pullup_en((gpio_num_t)SD_MISO);        // internal pull-up on MISO (an external 10k-47k is better)
        if (SD.begin(SD_CS, sdspi, f)) {
            sd_mounted = true;
            const char *t = SD.cardType() == CARD_MMC ? "MMC" : SD.cardType() == CARD_SD ? "SDSC"
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    SD.end();
    sdspi.end();
    sd_mounted = false;
    const int P[4] = {SD_CS, SD_SCK, SD_MOSI, SD_MISO};
    Serial.println("SD probe: CMD0 at ~100 kHz with every assignment of GPIO5/18/23/19 (expect answer 01)");
    int found = 0;
    int idx[4] = {0, 1, 2, 3};
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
